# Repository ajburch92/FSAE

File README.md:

# FSAE
Texas A&amp;M FSAE Electrical Team

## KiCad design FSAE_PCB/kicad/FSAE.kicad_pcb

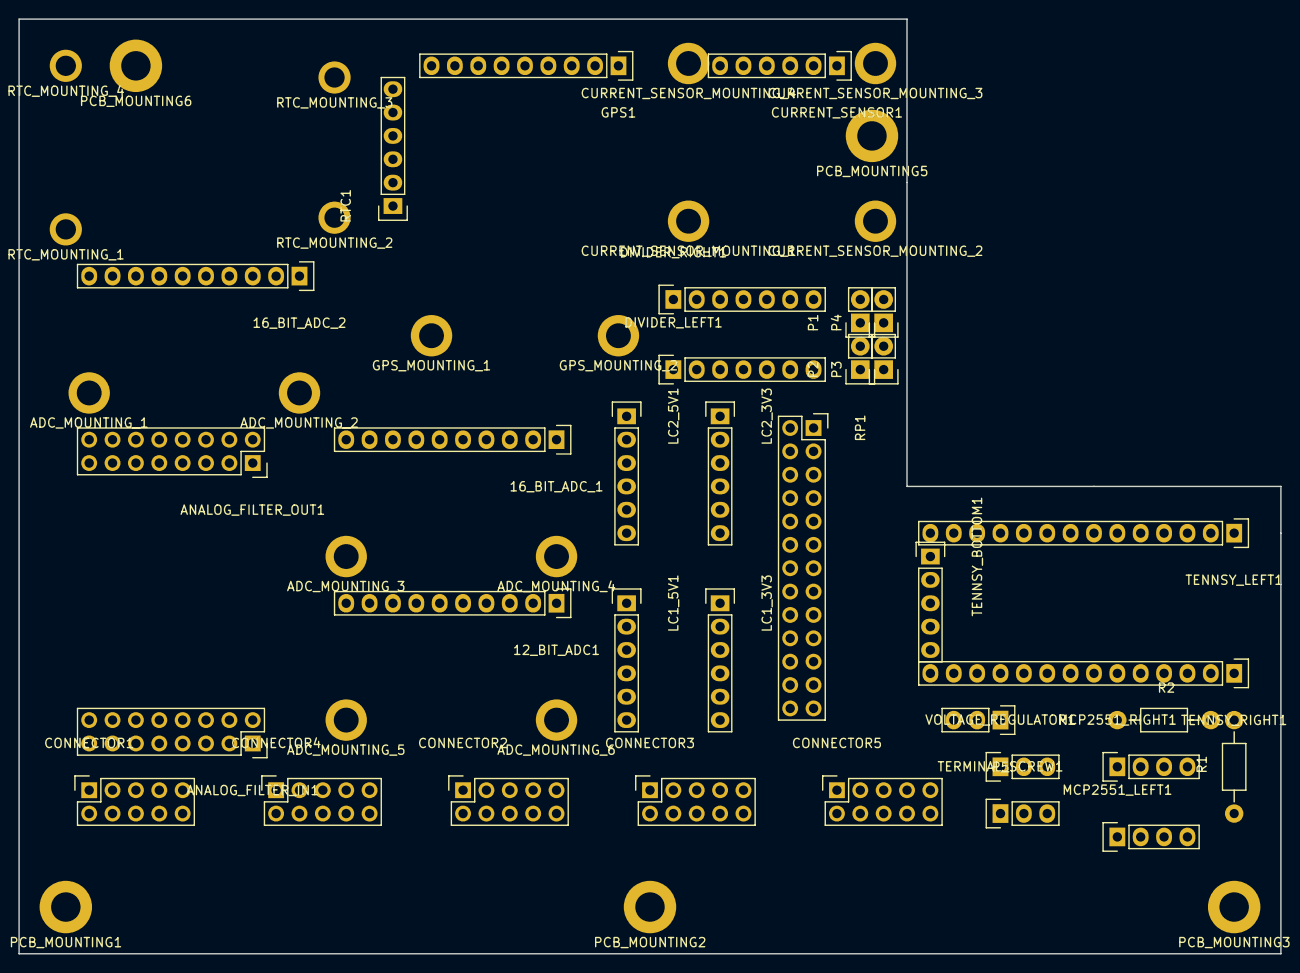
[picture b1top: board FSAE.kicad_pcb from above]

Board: 2 copper layers, 137.2 x 101.6 mm, 55 parts (0 on the bottom side), 42 nets, no tracks yet.

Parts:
12_BIT_ADC1, 16_BIT_ADC_1, 16_BIT_ADC_2: CONN_01X10; Socket_Strip_Straight_1x10
ADC_MOUNTING_1, ADC_MOUNTING_2, ADC_MOUNTING_3, ADC_MOUNTING_4, ADC_MOUNTING_5, ADC_MOUNTING_6: MountingHole_2.7mm_M2.5_ISO7380_Pad
ANALOG_FILTER_IN1: CONN_02X08; Socket_Strip_Straight_2x08
ANALOG_FILTER_OUT1: CONN_02X08; Socket_Strip_Straight_2x08
CONNECTOR1, CONNECTOR2, CONNECTOR3, CONNECTOR4, CONNECTOR5: CONN_02X05; Socket_Strip_Straight_2x05
CURRENT_SENSOR1: CONN_01X06; Socket_Strip_Straight_1x06
CURRENT_SENSOR_MOUNTING_1, CURRENT_SENSOR_MOUNTING_2, CURRENT_SENSOR_MOUNTING_3, CURRENT_SENSOR_MOUNTING_4: MountingHole_2.7mm_M2.5_ISO7380_Pad
DIVIDER_LEFT1: CONN_01X07; Socket_Strip_Straight_1x07
DIVIDER_RIGHT1: CONN_01X07; Socket_Strip_Straight_1x07
GPS1: CONN_01X09; Socket_Strip_Straight_1x09
GPS_MOUNTING_1, GPS_MOUNTING_2: MountingHole_2.7mm_M2.5_ISO7380_Pad
LC1_3V3, LC1_5V1, LC2_3V3, LC2_5V1: CONN_01X06; Socket_Strip_Straight_1x06
MCP2551_LEFT1, MCP2551_RIGHT1: CONN_01X04; Socket_Strip_Straight_1x04
P1, P2, P3, P4: CONN_01X02; Socket_Strip_Straight_1x02
P5: CONN_01X03; Socket_Strip_Straight_1x03
PCB_MOUNTING1, PCB_MOUNTING2, PCB_MOUNTING3, PCB_MOUNTING5, PCB_MOUNTING6: MountingHole_2.2mm_M2; MountingHole_3.2mm_M3_ISO7380_Pad
R1, R2: R; Resistor_Horizontal_RM10mm
RP1: CONN_02X13; Socket_Strip_Straight_2x13
RTC1: CONN_01X06; Socket_Strip_Straight_1x06
RTC_MOUNTING_1, RTC_MOUNTING_2, RTC_MOUNTING_3, RTC_MOUNTING_4: MountingHole_2.2mm_M2_ISO7380_Pad
TENNSY_BOTTOM1: CONN_01X05; Socket_Strip_Straight_1x05
TENNSY_LEFT1: CONN_01X14; Socket_Strip_Straight_1x14
TENNSY_RIGHT1: CONN_01X14; Socket_Strip_Straight_1x14
TERMINAL_SCREW1: CONN_01X03; Socket_Strip_Straight_1x03
VOLTAGE_REGULATOR1: CONN_01X03; Socket_Strip_Straight_1x03

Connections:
/3V3: CONNECTOR2.10, CONNECTOR3.6, CONNECTOR5.8, CURRENT_SENSOR1.1, GPS1.8, LC1_3V3.6, LC2_3V3.6, P5.2, RTC1.2, VOLTAGE_REGULATOR1.2
/5V: 12_BIT_ADC1.1, 16_BIT_ADC_1.1, 16_BIT_ADC_2.1, 16_BIT_ADC_2.5, ANALOG_FILTER_IN1.1, ANALOG_FILTER_OUT1.1, CONNECTOR1.8, CONNECTOR1.10, CONNECTOR3.2, CONNECTOR4.10, DIVIDER_LEFT1.5, LC1_5V1.6, LC2_5V1.6, MCP2551_LEFT1.2, P5.3, TERMINAL_SCREW1.3, VOLTAGE_REGULATOR1.3
/BL_SHOCK_POT_5V_IN: ANALOG_FILTER_IN1.15, CONNECTOR1.1
/BL_SHOCK_POT_5V_OUT: 12_BIT_ADC1.10, ANALOG_FILTER_OUT1.15
/BR_SHOCK_POT_5V_IN: ANALOG_FILTER_IN1.13, CONNECTOR1.3
/BR_SHOCK_POT_5V_OUT: 12_BIT_ADC1.9, ANALOG_FILTER_OUT1.13
/CAN_HI: CONNECTOR2.5, MCP2551_RIGHT1.2, R2.1
/CAN_LO: CONNECTOR2.3, MCP2551_RIGHT1.3, R2.2
/CKB_QA: DIVIDER_LEFT1.1, DIVIDER_RIGHT1.3, P1.2
/DASH_BUTTON_SR: CONNECTOR3.9, RP1.17
/DASH_LED_SR_3V3: CONNECTOR3.7, RP1.16
/FL_SHOCK_POT_5V_IN: ANALOG_FILTER_IN1.11, CONNECTOR1.5
/FL_SHOCK_POT_5V_OUT: 12_BIT_ADC1.8, ANALOG_FILTER_OUT1.11
/FRONT_BRAKE_+_IN: CONNECTOR4.3, CURRENT_SENSOR1.6
/FRONT_BRAKE_-_IN: CONNECTOR4.5, CURRENT_SENSOR1.5
/FR_SHOCK_POT_5V_IN: ANALOG_FILTER_IN1.9, CONNECTOR1.7
/FR_SHOCK_POT_5V_OUT: 12_BIT_ADC1.7, ANALOG_FILTER_OUT1.9
/FUEL_IN: ANALOG_FILTER_IN1.3, CONNECTOR2.1
/FUEL_OUT: 16_BIT_ADC_1.7, ANALOG_FILTER_OUT1.3
/GND: 12_BIT_ADC1.2, 12_BIT_ADC1.5, 16_BIT_ADC_1.2, 16_BIT_ADC_2.2, ANALOG_FILTER_IN1.16, ANALOG_FILTER_OUT1.16, CONNECTOR1.2, CONNECTOR1.4, CONNECTOR2.6, CONNECTOR3.10, CONNECTOR4.6, CONNECTOR5.4, CURRENT_SENSOR1.2, DIVIDER_RIGHT1.5, GPS1.7, LC1_3V3.1, LC1_5V1.1, LC2_3V3.1, LC2_5V1.1, MCP2551_LEFT1.3, R1.1, RP1.10, RTC1.1, TENNSY_LEFT1.1, TERMINAL_SCREW1.1, VOLTAGE_REGULATOR1.1
/INTERRUPT: P3.1, P3.2, P4.1, P4.2, RP1.21
/PITOT_TUBE_IN: ANALOG_FILTER_IN1.14, CONNECTOR4.2
/PITOT_TUBE_OUT: 16_BIT_ADC_2.8, ANALOG_FILTER_OUT1.14
/QB: DIVIDER_RIGHT1.4, P1.1
/QC: DIVIDER_RIGHT1.6, P2.2
/QD: DIVIDER_RIGHT1.7, P2.1
/REAR_BRAKE_+_IN: ANALOG_FILTER_IN1.6, CONNECTOR4.7
/REAR_BRAKE_+_OUT: 16_BIT_ADC_2.9, ANALOG_FILTER_OUT1.6
/REAR_BREAK_-_IN: ANALOG_FILTER_IN1.4, CONNECTOR4.9
/RX(RPI): GPS1.5, RP1.9
/RX_CAN: MCP2551_LEFT1.4, TENNSY_LEFT1.5
/SCL_3V3: CONNECTOR2.7, CONNECTOR5.3, CURRENT_SENSOR1.3, LC1_3V3.4, RP1.6, RTC1.4
/SCL_3V3_TEENSY: LC2_3V3.4, TENNSY_RIGHT1.8
/SCL_5V: 12_BIT_ADC1.3, 16_BIT_ADC_1.3, 16_BIT_ADC_2.3, LC1_5V1.4, LC2_5V1.4
/SDA_3V3: CONNECTOR2.9, CONNECTOR5.7, CURRENT_SENSOR1.4, LC1_3V3.5, RP1.4, RTC1.3
/SDA_3V3_TEENSY: LC2_3V3.5, TENNSY_RIGHT1.7
/SDA_5V: 12_BIT_ADC1.4, 16_BIT_ADC_1.4, 16_BIT_ADC_1.5, 16_BIT_ADC_2.4, LC1_5V1.5, LC2_5V1.5
/SQW: DIVIDER_RIGHT1.1, RTC1.5
/STEERING_SIGNAL_IN: ANALOG_FILTER_IN1.12, CONNECTOR4.1
/STEERING_SIGNAL_OUT: 16_BIT_ADC_2.7, ANALOG_FILTER_OUT1.12
/TX(RPI): GPS1.6, RP1.7
/TX_CAN: MCP2551_LEFT1.1, TENNSY_LEFT1.4

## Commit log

2016-01-18 MAIN.cpp
2016-01-21 Rename MAIN.cpp to MAIN2.cpp
    Updated Jan 21
2017-05-08 long overdue folder update
2017-05-08 file management
